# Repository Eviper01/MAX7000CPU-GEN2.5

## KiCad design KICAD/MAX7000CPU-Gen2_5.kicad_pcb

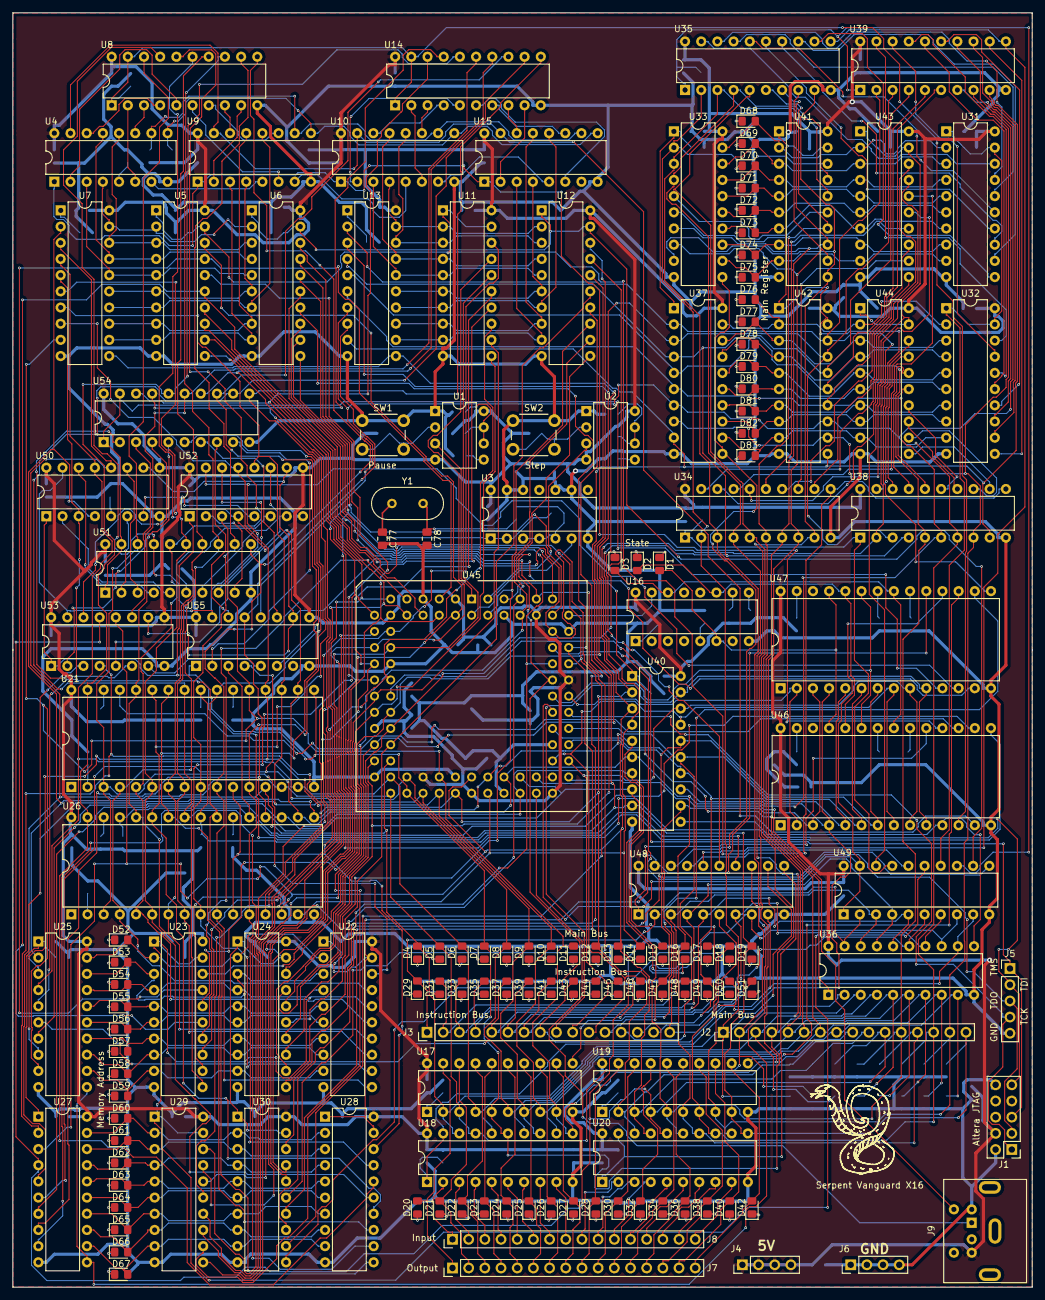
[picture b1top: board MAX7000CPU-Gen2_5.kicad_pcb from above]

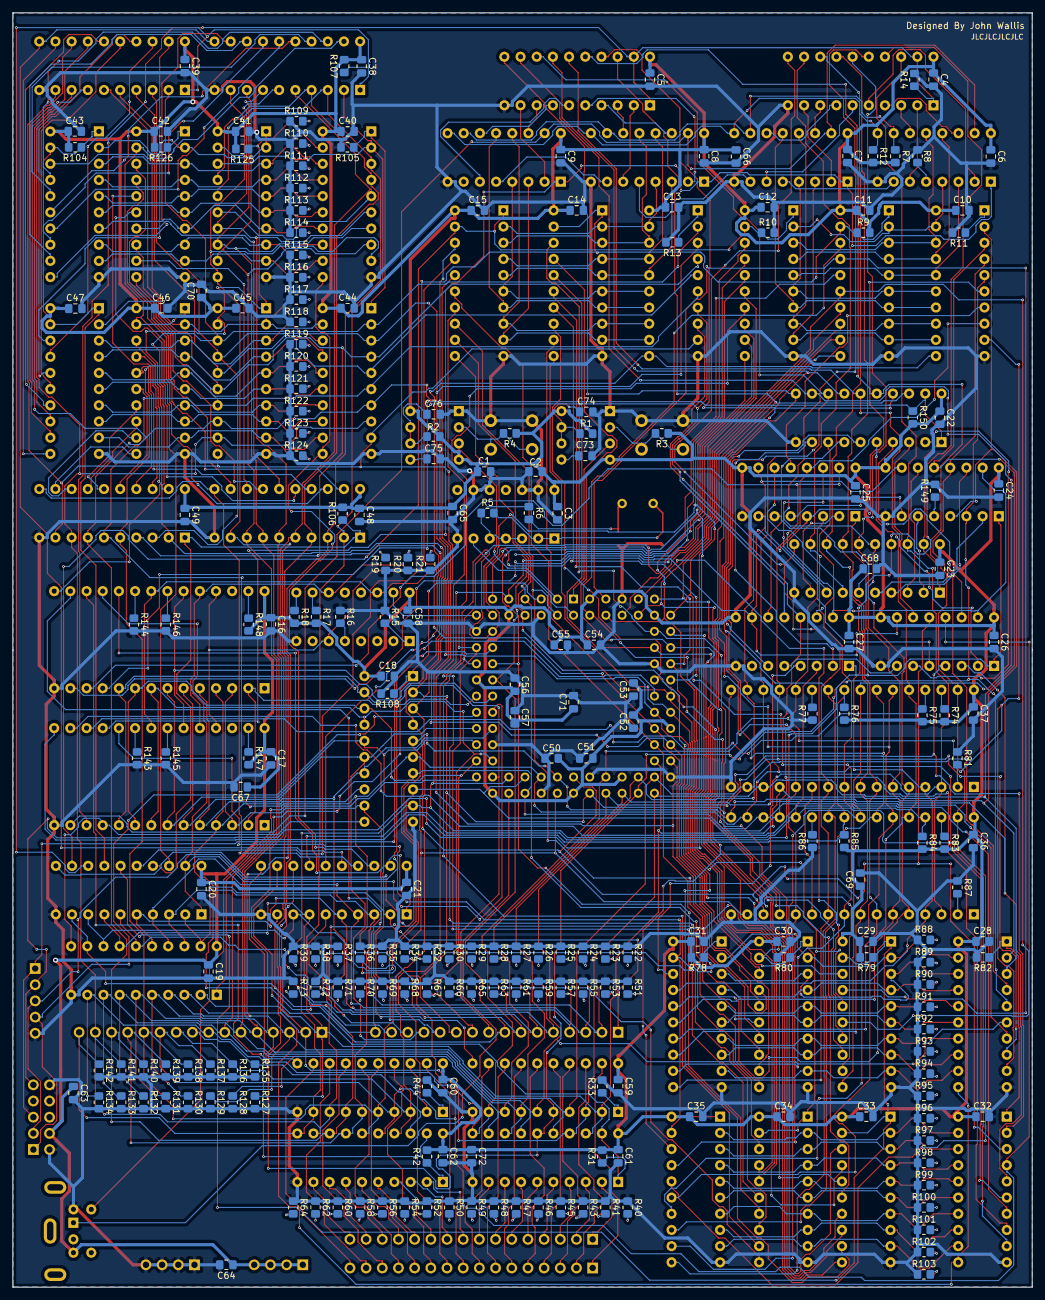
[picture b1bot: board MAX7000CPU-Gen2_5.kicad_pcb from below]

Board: 2 copper layers, 160.0 x 200.0 mm, 378 parts (226 on the bottom side), 398 nets.

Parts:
C1, C2, C3, C4, C5, C6, C7, C8, C9, C10, C11, C12, C13, C14, C15, C16, C17, C18, C19, C20, C21, C22, C23, C24, C25, C26, C27, C28, C29, C30, C31, C32, C33, C34, C35, C36, C37, C38, C39, C40, C41, C42, C43, C44, C45, C46, C47, C48, C49, C50, C51, C52, C53, C54, C55, C56, C57, C58, C59, C60, C61, C62, C63, C64, C74, C76: 100n; C_0805_2012Metric_Pad1.18x1.45mm_HandSolder
C65, C66, C67, C68, C69, C70, C71, C72: 10u; C_0805_2012Metric_Pad1.18x1.45mm_HandSolder
C73, C75: 10n; C_0805_2012Metric_Pad1.18x1.45mm_HandSolder
C77, C78: 33p; C_0805_2012Metric_Pad1.18x1.45mm_HandSolder
D1, D2, D3, D4, D5, D6, D7, D8, D9, D10, D11, D12, D13, D14, D15, D16, D17, D18, D19, D20, D21, D22, D23, D24, D25, D26, D27, D28, D29, D30, D31, D32, D33, D34, D35, D36, D37, D38, D39, D40, D41, D42, D43, D44, D45, D46, D47, D48, D49, D50, D51, D52, D53, D54, D55, D56, D57, D58, D59, D60, D61, D62, D63, D64, D65, D66, D67, D68, D69, D70, D71, D72, D73, D74, D75, D76, D77, D78, D79, D80, D81, D82, D83: LED; LED_0805_2012Metric_Pad1.15x1.40mm_HandSolder
J1: Conn_02x05_Odd_Even; PinHeader_2x05_P2.54mm_Vertical
J2, J3, J7, J8: Conn_01x16_Male; PinHeader_1x16_P2.54mm_Vertical
J4, J6: Conn_01x04_Male; PinHeader_1x04_P2.54mm_Vertical
J5: Conn_01x05_Male; PinHeader_1x05_P2.54mm_Vertical
J9: Mini-DIN-6; Connector_Mini-DIN_Female_6Pin_2rows
R1, R2, R5: 1M; R_0805_2012Metric_Pad1.20x1.40mm_HandSolder
R3, R4: 1K; R_0805_2012Metric_Pad1.20x1.40mm_HandSolder
R6: 4.7K; R_0805_2012Metric_Pad1.20x1.40mm_HandSolder
R7, R8, R9, R10, R11, R12, R13, R14, R15, R16, R17, R18, R31, R33, R42, R44, R74, R75, R76, R77, R78, R79, R80, R81, R82, R83, R84, R85, R86, R87, R104, R105, R106, R107, R108, R125, R126, R127, R128, R129, R130, R131, R132, R133, R134, R135, R136, R137, R138, R139, R140, R141, R142, R143, R144, R145, R146, R147, R148, R149, R150: 50K; R_0805_2012Metric_Pad1.20x1.40mm_HandSolder
R19, R20, R21, R22, R23, R24, R25, R26, R27, R28, R29, R30, R32, R34, R35, R36, R37, R38, R39, R40, R41, R43, R45, R46, R47, R48, R49, R50, R51, R52, R53, R54, R55, R56, R57, R58, R59, R60, R61, R62, R63, R64, R65, R66, R67, R68, R69, R70, R71, R72, R73, R88, R89, R90, R91, R92, R93, R94, R95, R96, R97, R98, R99, R100, R101, R102, R103, R109, R110, R111, R112, R113, R114, R115, R116, R117, R118, R119, R120, R121, R122, R123, R124: 330; R_0805_2012Metric_Pad1.20x1.40mm_HandSolder
SW1, SW2: SW_Push; SW_PUSH_6mm
U1, U2: NE555P; DIP-8_W7.62mm
U3: 74HC00; DIP-14_W7.62mm
U4, U9, U10, U15, U16, U50, U52, U53, U55: CD4029BEE4; DIP-16_W7.62mm
U5, U6, U8, U11, U12, U14, U18, U20, U22, U23, U24, U28, U29, U30, U31, U32, U41, U42, U43, U44, U48, U49, U51, U54: 74LS541; DIP-20_W7.62mm
U7, U13, U17, U19, U25, U27, U33, U34, U35, U36, U37, U38, U39, U40: 74LS574; DIP-20_W7.62mm
U21, U26: AS6C1008-55PCN; DIP-32_W15.24mm
U45: EPM7128slc84-15n; PLCC-84_THT-Socket
U46, U47: AT28C64B-15PU; DIP-28_W15.24mm
Y1: Crystal; Crystal_HC49-U_Vertical

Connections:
+5V: C1.1, C2.1, C3.1, C4.1, C5.1, C6.1, C7.1, C8.1, C9.1, C10.1, C11.1, C12.1, C13.1, C14.1, C15.1, C16.1, C17.1, C18.1, C19.1, C20.1, C21.1, C22.1, C23.1, C24.1, C25.1, C26.1, C27.1, C28.1, C29.1, C30.1, C31.1, C32.1, C33.1, C34.1, C35.1, C36.1, C37.1, C38.1, C39.1, C40.1, C41.1, C42.1, C43.1, C44.1, C45.1, C46.1, C47.1, C48.1, C49.1, C50.1, C51.1, C52.1, C53.1, C54.1, C55.1, C56.1, C57.1, C58.1, C59.1, C60.1, C61.1, C62.1, C63.1, C64.1, C65.1, C66.1, C67.1, C68.1, C69.1, C70.1, C71.1, C72.1, J1.4, J4.1, J4.2, J4.3, J4.4, J9.4, R1.1, R2.1, R3.1, R4.1, R7.2, R9.2, R12.2, R17.2, R18.2, R31.2, R42.2, R74.2, R75.2, R76.2, R78.2, R79.2, R83.2, R84.2, R85.2, R104.2, R106.2, R107.2, R125.2, R126.2, R147.2, R148.2, R150.2, U1.4, U1.8, U2.4, U2.8, U3.14, U4.16, U5.20, U6.20, U7.20, U8.20, U9.16, U10.16, U11.20, U12.20, U13.20, U14.20, U15.16, U16.16, U17.20, U18.20, U19.20, U20.20, U21.32, U22.20, U23.20, U24.20, U25.20, U26.32, U27.20, U28.20, U29.20, U30.20, U31.20, U32.20, U33.20, U34.20, U35.20, U36.20, U37.20, U38.20, U39.20, U40.20, U41.20, U42.20, U43.20, U44.20, U45.3, U45.13, U45.26, U45.38, U45.43, U45.53, U45.66, U45.78, U46.28, U47.28, U48.20, U49.20, U50.9, U50.16, U51.20, U52.9, U52.16, U53.9, U53.16, U54.20, U55.9, U55.16
/ALU/B0: D4.2, J2.1, R127.1, U7.2, U17.2, U18.18, U21.13, U25.2, U33.2, U34.2, U35.2, U36.2, U41.18, U45.31, U50.4
/ALU/B1: D5.2, J2.2, R128.1, U7.3, U17.3, U18.17, U21.14, U25.3, U33.3, U34.3, U35.3, U36.3, U41.17, U45.33, U50.12
/ALU/B2: D6.2, J2.3, R129.1, U7.4, U17.4, U18.16, U21.15, U25.4, U33.4, U34.4, U35.4, U36.4, U41.16, U45.34, U50.13
/ALU/B3: D7.2, J2.4, R130.1, U7.5, U17.5, U18.15, U21.17, U25.5, U33.5, U34.5, U35.5, U36.5, U41.15, U45.35, U50.3
/ALU/B4: D8.2, J2.5, R131.1, U7.6, U17.6, U18.14, U21.18, U25.6, U33.6, U34.6, U35.6, U36.6, U41.14, U45.36, U52.4
/ALU/B5: D9.2, J2.6, R132.1, U7.7, U17.7, U18.13, U21.19, U25.7, U33.7, U34.7, U35.7, U36.7, U41.13, U45.37, U52.12
/ALU/B6: D10.2, J2.7, R133.1, U7.8, U17.8, U18.12, U21.20, U25.8, U33.8, U34.8, U35.8, U36.8, U41.12, U45.39, U52.13
/ALU/B7: D11.2, J2.8, R134.1, U7.9, U17.9, U18.11, U21.21, U25.9, U33.9, U34.9, U35.9, U36.9, U41.11, U45.40, U52.3
/ALU/B8: D12.2, J2.9, R135.1, U13.2, U19.2, U20.18, U26.13, U27.2, U37.2, U38.2, U39.2, U40.2, U42.18, U45.41, U53.4
/ALU/B9: D13.2, J2.10, R136.1, U13.3, U19.3, U20.17, U26.14, U27.3, U37.3, U38.3, U39.3, U40.3, U42.17, U45.44, U53.12
/ALU/B10: D14.2, J2.11, R137.1, U13.4, U19.4, U20.16, U26.15, U27.4, U37.4, U38.4, U39.4, U40.4, U42.16, U45.45, U53.13
/ALU/B11: D15.2, J2.12, R138.1, U13.5, U19.5, U20.15, U26.17, U27.5, U37.5, U38.5, U39.5, U40.5, U42.15, U45.46, U53.3
/ALU/B12: D16.2, J2.13, R139.1, U13.6, U19.6, U20.14, U26.18, U27.6, U37.6, U38.6, U39.6, U40.6, U42.14, U45.48, U55.4
/ALU/B13: D17.2, J2.14, R140.1, U13.7, U19.7, U20.13, U26.19, U27.7, U37.7, U38.7, U39.7, U40.7, U42.13, U45.49, U55.12
/ALU/B14: D18.2, J2.15, R141.1, U13.8, U19.8, U20.12, U26.20, U27.8, U37.8, U38.8, U39.8, U40.8, U42.12, U45.50, U55.13
/ALU/B15: D19.2, J2.16, R142.1, U13.9, U19.9, U20.11, U26.21, U27.9, U37.9, U38.9, U39.9, U40.9, U42.11, U45.52, U55.3
/ALU/Ins0: D29.2, J3.1, U36.19, U48.2, U49.2
/ALU/Ins1: D31.2, J3.2, U36.18, U48.3, U49.3
/ALU/Ins2: D33.2, J3.3, U36.17, U48.4, U49.4
/ALU/Ins3: D35.2, J3.4, U36.16, U48.5, U49.5
/ALU/Ins4: D37.2, J3.5, U36.15, U48.6, U49.6
/ALU/Ins5: D39.2, J3.6, U36.14, U48.7, U49.7
/ALU/Ins6: D41.2, J3.7, U36.13, U48.8, U49.8
/ALU/Ins7: D43.2, J3.8, U36.12, U48.9, U49.9
/ALU/Ins8: D44.2, J3.9, U40.19, U45.55, U46.10, U47.10
/ALU/Ins9: D45.2, J3.10, U40.18, U45.56, U46.9, U47.9
/ALU/Ins10: D46.2, J3.11, U40.17, U45.57, U46.8, U47.8
/ALU/Ins11: D47.2, J3.12, U40.16, U45.58, U46.7, U47.7
/ALU/Ins12: D48.2, J3.13, U40.15, U45.60, U46.6, U47.6
/ALU/Ins13: D49.2, J3.14, U40.14, U45.61, U46.5, U47.5
/ALU/Ins14: D50.2, J3.15, U40.13, U46.4, U47.4
/ALU/Ins15: D51.2, J3.16, U40.12, U46.3, U47.3
/ALU/r_A0: U5.18, U23.18, U45.4
/ALU/r_A1: U5.17, U23.17, U45.5
/ALU/r_A2: U5.16, U23.16, U45.6
/ALU/r_A3: U5.15, U23.15, U45.8
/ALU/r_A4: U5.14, U23.14, U45.9
/ALU/r_A5: U5.13, U23.13, U45.10
/ALU/r_A6: U5.12, U23.12, U45.11
/ALU/r_A7: U5.11, U23.11, U45.12
/ALU/r_A8: U11.18, U29.18, U45.15
/ALU/r_A9: U11.17, U29.17, U45.16
/ALU/r_A10: U11.16, U29.16, U45.17
/ALU/r_A11: U11.15, U29.15, U45.18
/ALU/r_A12: U11.14, U29.14, U45.20
/ALU/r_A13: U11.13, U29.13, U45.21
/ALU/r_A14: U11.12, U29.12, U45.22
/ALU/r_A15: U11.11, U29.11, U45.24
/ALU/r_B0: U12.18, U24.18, U45.25
/ALU/r_B1: U12.17, U24.17, U45.27
/ALU/r_B2: U12.16, U24.16, U45.28
/ALU/r_B3: U12.15, U24.15, U45.29
/ALU/r_B4: U12.14, U24.14, U45.30
/ALU/r_B5: U12.13, U24.13, U45.84
/ALU/r_B6: U12.12, U24.12, U45.80
/ALU/r_B7: U12.11, U24.11, U45.79
/ALU/r_B8: U6.18, U30.18, U45.77
/ALU/r_B9: U6.17, U30.17, U45.76
/ALU/r_B10: U6.16, U30.16, U45.75
/ALU/r_B11: U6.15, U30.15, U45.73
/ALU/r_B12: U6.14, U30.14, U45.70
/ALU/r_B13: U6.13, U30.13, U45.69
/ALU/r_B14: U6.12, U30.12, U45.68
/ALU/r_B15: U6.11, U30.11, U45.67
/Counter Module/JB0: U4.4, U5.2, U6.2, U7.19
/Counter Module/JB1: U4.12, U5.3, U6.3, U7.18
/Counter Module/JB2: U4.13, U5.4, U6.4, U7.17
/Counter Module/JB3: U4.3, U5.5, U6.5, U7.16
/Counter Module/JB4: U5.6, U6.6, U7.15, U9.4
/Counter Module/JB5: U5.7, U6.7, U7.14, U9.12
/Counter Module/JB6: U5.8, U6.8, U7.13, U9.13
/Counter Module/JB7: U5.9, U6.9, U7.12, U9.3
/Counter Module/JB8: U10.4, U11.2, U12.2, U13.19
/Counter Module/JB9: U10.12, U11.3, U12.3, U13.18
/Counter Module/JB10: U10.13, U11.4, U12.4, U13.17
/Counter Module/JB11: U10.3, U11.5, U12.5, U13.16
/Counter Module/JB12: U11.6, U12.6, U13.15, U15.4
/Counter Module/JB13: U11.7, U12.7, U13.14, U15.12
/Counter Module/JB14: U11.8, U12.8, U13.13, U15.13
/Counter Module/JB15: U11.9, U12.9, U13.12, U15.3
/Counter Module/RA0: U8.18, U21.3, U22.18, U26.3, U51.18
/Counter Module/RA1: U8.17, U21.4, U22.17, U26.4, U51.17
/Counter Module/RA2: U8.16, U21.5, U22.16, U26.5, U51.16
/Counter Module/RA3: U8.15, U21.6, U22.15, U26.6, U51.15
/Counter Module/RA4: U8.14, U21.7, U22.14, U26.7, U51.14
/Counter Module/RA5: U8.13, U21.8, U22.13, U26.8, U51.13
/Counter Module/RA6: U8.12, U21.9, U22.12, U26.9, U51.12
/Counter Module/RA7: U8.11, U21.10, U22.11, U26.10, U51.11
/Counter Module/RA8: U14.18, U21.11, U26.11, U28.18, U54.18
/Counter Module/RA9: U14.17, U21.12, U26.12, U28.17, U54.17
/Counter Module/RA10: U14.16, U21.31, U26.31, U28.16, U54.16
/Counter Module/RA11: U14.15, U21.28, U26.28, U28.15, U54.15
/Counter Module/RA12: U14.14, U21.27, U26.27, U28.14, U54.14
/Counter Module/RA13: U14.13, U21.26, U26.26, U28.13, U54.13
/Counter Module/RA14: U14.12, U21.25, U26.25, U28.12, U54.12
/Counter Module/RA15: U14.11, U21.23, U26.23, U28.11, U54.11
/Counter Module/State0: D1.2, U16.6, U46.25, U47.25
/Counter Module/State1: D2.2, U16.11, U46.24, U47.24
/Counter Module/State2: D3.2, U16.14, U46.21, U47.21
/Interface/PI0: J8.1, U18.2
/Interface/PI1: J8.2, U18.3
/Interface/PI2: J8.3, U18.4
/Interface/PI3: J8.4, U18.5
/Interface/PI4: J8.5, U18.6
/Interface/PI5: J8.6, U18.7
/Interface/PI6: J8.7, U18.8
/Interface/PI7: J8.8, U18.9
/Interface/PI8: J8.9, U20.2
/Interface/PI9: J8.10, U20.3
/Interface/PI10: J8.11, U20.4
/Interface/PI11: J8.12, U20.5
/Interface/PI12: J8.13, U20.6
/Interface/PI13: J8.14, U20.7
/Interface/PI14: J8.15, U20.8
/Interface/PI15: J8.16, U20.9
/Interface/PO0: D20.2, J7.1, U17.19
/Interface/PO1: D21.2, J7.2, U17.18
/Interface/PO2: D22.2, J7.3, U17.17
/Interface/PO3: D23.2, J7.4, U17.16
/Interface/PO4: D24.2, J7.5, U17.15
/Interface/PO5: D25.2, J7.6, U17.14
/Interface/PO6: D26.2, J7.7, U17.13
/Interface/PO7: D27.2, J7.8, U17.12
/Interface/PO8: D28.2, J7.9, U19.19
/Interface/PO9: D30.2, J7.10, U19.18
/Interface/PO10: D32.2, J7.11, U19.17
/Interface/PO11: D34.2, J7.12, U19.16
/Interface/PO12: D36.2, J7.13, U19.15
/Interface/PO13: D38.2, J7.14, U19.14
/Interface/PO14: D40.2, J7.15, U19.13
/Interface/PO15: D42.2, J7.16, U19.12
/Memory/MA0: D52.2, U22.2, U23.2, U24.2, U25.19
/Memory/MA1: D53.2, U22.3, U23.3, U24.3, U25.18
/Memory/MA2: D54.2, U22.4, U23.4, U24.4, U25.17
/Memory/MA3: D55.2, U22.5, U23.5, U24.5, U25.16
/Memory/MA4: D56.2, U22.6, U23.6, U24.6, U25.15
/Memory/MA5: D57.2, U22.7, U23.7, U24.7, U25.14
/Memory/MA6: D58.2, U22.8, U23.8, U24.8, U25.13
/Memory/MA7: D59.2, U22.9, U23.9, U24.9, U25.12
/Memory/MA8: D60.2, U27.19, U28.2, U29.2, U30.2
/Memory/MA9: D61.2, U27.18, U28.3, U29.3, U30.3
/Memory/MA10: D62.2, U27.17, U28.4, U29.4, U30.4
/Memory/MA11: D63.2, U27.16, U28.5, U29.5, U30.5
/Memory/MA12: D64.2, U27.15, U28.6, U29.6, U30.6
/Memory/MA13: D65.2, U27.14, U28.7, U29.7, U30.7
/Memory/MA14: D66.2, U27.13, U28.8, U29.8, U30.8
/Memory/MA15: D67.2, U27.12, U28.9, U29.9, U30.9
/Registers/MR0: D68.2, U31.2, U33.19, U41.2, U43.2
/Registers/MR1: D69.2, U31.3, U33.18, U41.3, U43.3
/Registers/MR2: D70.2, U31.4, U33.17, U41.4, U43.4
/Registers/MR3: D71.2, U31.5, U33.16, U41.5, U43.5
/Registers/MR4: D72.2, U31.6, U33.15, U41.6, U43.6
/Registers/MR5: D73.2, U31.7, U33.14, U41.7, U43.7
/Registers/MR6: D74.2, U31.8, U33.13, U41.8, U43.8
/Registers/MR7: D75.2, U31.9, U33.12, U41.9, U43.9
/Registers/MR8: D76.2, U32.2, U37.19, U42.2, U44.2
/Registers/MR9: D77.2, U32.3, U37.18, U42.3, U44.3
/Registers/MR10: D78.2, U32.4, U37.17, U42.4, U44.4
/Registers/MR11: D79.2, U32.5, U37.16, U42.5, U44.5
/Registers/MR12: D80.2, U32.6, U37.15, U42.6, U44.6
/Registers/MR13: D81.2, U32.7, U37.14, U42.7, U44.7
/Registers/MR14: D82.2, U32.8, U37.13, U42.8, U44.8
/Registers/MR15: D83.2, U32.9, U37.12, U42.9, U44.9
/Registers/rA0: U34.19, U43.18
/Registers/rA1: U34.18, U43.17
/Registers/rA2: U34.17, U43.16
/Registers/rA3: U34.16, U43.15
/Registers/rA4: U34.15, U43.14
/Registers/rA5: U34.14, U43.13
/Registers/rA6: U34.13, U43.12
/Registers/rA7: U34.12, U43.11
/Registers/rA8: U38.19, U44.18
/Registers/rA9: U38.18, U44.17
/Registers/rA10: U38.17, U44.16
/Registers/rA11: U38.16, U44.15
/Registers/rA12: U38.15, U44.14
/Registers/rA13: U38.14, U44.13
/Registers/rA14: U38.13, U44.12
/Registers/rA15: U38.12, U44.11
/Registers/rB0: U31.18, U35.19
/Registers/rB1: U31.17, U35.18
/Registers/rB2: U31.16, U35.17
/Registers/rB3: U31.15, U35.16
/Registers/rB4: U31.14, U35.15
/Registers/rB5: U31.13, U35.14
/Registers/rB6: U31.12, U35.13
/Registers/rB7: U31.11, U35.12
/Registers/rB8: U32.18, U39.19
/Registers/rB9: U32.17, U39.18
/Registers/rB10: U32.16, U39.17
/Registers/rB11: U32.15, U39.16
/Registers/rB12: U32.14, U39.15
/Registers/rB13: U32.13, U39.14
/Registers/rB14: U32.12, U39.13
/Registers/rB15: U32.11, U39.12
ALU_Regs: U45.63, U47.18, U49.1, U49.19
CLK: U16.15, U45.74
CLK_Select: U1.3, U45.1
Count: U4.15, U9.15, U10.15, U15.15, U46.13
CounterOutControl: R14.1, U8.1, U8.19, U14.1, U14.19, U46.12
EqualFlag: U45.65, U46.23, U47.23
FastCLK: U3.6, U45.2
GND: C1.2, C2.2, C3.2, C4.2, C5.2, C6.2, C7.2, C8.2, C9.2, C10.2, C11.2, C12.2, C13.2, C14.2, C15.2, C16.2, C17.2, C18.2, C19.2, C20.2, C21.2, C22.2, C23.2, C24.2, C25.2, C26.2, C27.2, C28.2, C29.2, C30.2, C31.2, C32.2, C33.2, C34.2, C35.2, C36.2, C37.2, C38.2, C39.2, C40.2, C41.2, C42.2, C43.2, C44.2, C45.2, C46.2, C47.2, C48.2, C49.2, C50.2, C51.2, C52.2, C53.2, C54.2, C55.2, C56.2, C57.2, C58.2, C59.2, C60.2, C61.2, C62.2, C63.2, C64.2, C65.2, C66.2, C67.2, C68.2, C69.2, C70.2, C71.2, C72.2, C73.2, C74.2, C75.2, C76.2, C77.2, C78.2, J1.2, J1.10, J5.5, J6.1, J6.2, J6.3, J6.4, J9.3, R8.2, R10.2, R11.2, R13.2, R14.2, R15.2, R16.2, R19.1, R20.1, R21.1, R22.1, R23.1, R24.1, R25.1, R26.1, R27.1, R28.1, R29.1, R30.1, R32.1, R33.2, R34.1, R35.1, R36.1, R37.1, R38.1, R39.1, R40.1, R41.1, R43.1, R44.2, R45.1, R46.1, R47.1, R48.1, R49.1, R50.1, R51.1, R52.1, R53.1, R54.1, R55.1, R56.1, R57.1, R58.1, R59.1, R60.1, R61.1, R62.1, R63.1, R64.1, R65.1, R66.1, R67.1, R68.1, R69.1, R70.1, R71.1, R72.1, R73.1, R77.1, R80.2, R81.1, R82.2, R86.1, R87.1, R88.1, R89.1, R90.1, R91.1, R92.1, R93.1, R94.1, R95.1, R96.1, R97.1, R98.1, R99.1, R100.1, R101.1, R102.1, R103.1, R105.2, R108.2, R109.1, R110.1, R111.1, R112.1, R113.1, R114.1, R115.1, R116.1, R117.1, R118.1, R119.1, R120.1, R121.1, R122.1, R123.1, R124.1, R127.2, R128.2, R129.2, R130.2, R131.2, R132.2, R133.2, R134.2, R135.2, R136.2, R137.2, R138.2, R139.2, R140.2, R141.2, R142.2, R143.2, R144.2, R145.2, R146.2, R149.2, SW1.1, SW2.1, U1.1, U2.1, U3.7, U3.9, U3.10, U3.12, U3.13, U4.8, U5.10, U6.10, U7.10, U8.10, U9.8, U10.8, U11.10, U12.10, U13.10, U14.10, U15.8, U16.8, U17.10, U18.10, U19.10, U20.10, U21.16, U22.10, U23.10, U24.10, U25.10, U26.16, U27.10, U28.10, U29.10, U30.10, U31.10, U32.10, U33.10, U34.10, U35.10, U36.10, U37.10, U38.10, U39.10, U40.10, U41.10, U42.10, U43.10, U44.10, U45.7, U45.19, U45.32, U45.42, U45.47, U45.59, U45.72, U45.82, U46.14, U47.14, U48.10, U49.10, U50.8, U51.10, U52.8, U53.8, U54.10, U55.8
I2CCLK: J9.5, U45.54
I2CData: J9.1, U45.51
InsRegControl: U36.11, U40.11, U46.11
JumpBufferAOutput: R9.1, U5.1, U5.19, U11.1, U11.19, U49.16
JumpBufferBOutput: R10.1, U6.1, U6.19, U12.1, U12.19, U49.12
JumpEnable: U4.1, U9.1, U10.1, U15.1, U46.18
JumpRegLoad: U7.11, U13.11, U48.15
MainAOutput: R126.1, U43.1, U43.19, U44.1, U44.19, U49.18
MainBOutput: R104.1, U31.1, U31.19, U32.1, U32.19, U49.14
MainRegOutputControl: R125.1, U41.1, U41.19, U42.1, U42.19, U47.15
MainRegReadControl: U33.11, U37.11, U48.18
MemAddrAOutput: R79.1, U23.1, U23.19, U29.1, U29.19, U49.15
MemAddrBOutput: R80.1, U24.1, U24.19, U30.1, U30.19, U49.11
MemOutEnable: R76.1, R85.1, U21.24, U26.24, U46.15
MemWriteControlH: R84.1, U26.29, U46.16
MemWriteControlL: R75.1, U21.29, U46.17
unnamed: C73.1, U1.5
unnamed: C74.1, R1.2, U1.6, U1.7
unnamed: C75.1, U2.5
unnamed: C76.1, R2.2, U2.6, U2.7
unnamed: C77.1, R5.2, U3.1, U3.2, Y1.1
unnamed: C78.1, R6.2, Y1.2
unnamed: D1.1, R19.2
unnamed: D2.1, R20.2
unnamed: D3.1, R21.2
unnamed: D4.1, R22.2
unnamed: D5.1, R23.2
unnamed: D6.1, R24.2
unnamed: D7.1, R25.2
unnamed: D8.1, R26.2
unnamed: D9.1, R27.2
unnamed: D10.1, R28.2
unnamed: D11.1, R29.2
unnamed: D12.1, R30.2
unnamed: D13.1, R32.2
unnamed: D14.1, R34.2
unnamed: D15.1, R35.2
unnamed: D16.1, R36.2
unnamed: D17.1, R37.2
unnamed: D18.1, R38.2
unnamed: D19.1, R39.2
unnamed: D20.1, R40.2
unnamed: D21.1, R41.2
unnamed: D22.1, R43.2
unnamed: D23.1, R45.2
unnamed: D24.1, R46.2
unnamed: D25.1, R47.2
unnamed: D26.1, R48.2
unnamed: D27.1, R49.2
unnamed: D28.1, R50.2
unnamed: D29.1, R51.2
unnamed: D30.1, R52.2
unnamed: D31.1, R53.2
unnamed: D32.1, R54.2
unnamed: D33.1, R55.2
unnamed: D34.1, R56.2
unnamed: D35.1, R57.2
unnamed: D36.1, R58.2
unnamed: D37.1, R59.2
unnamed: D38.1, R60.2
unnamed: D39.1, R61.2
unnamed: D40.1, R62.2
unnamed: D41.1, R63.2
unnamed: D42.1, R64.2
unnamed: D43.1, R65.2
unnamed: D44.1, R66.2
unnamed: D45.1, R67.2
unnamed: D46.1, R68.2
unnamed: D47.1, R69.2
unnamed: D48.1, R70.2
unnamed: D49.1, R71.2
unnamed: D50.1, R72.2
unnamed: D51.1, R73.2
unnamed: D52.1, R88.2
unnamed: D53.1, R89.2
unnamed: D54.1, R90.2
unnamed: D55.1, R91.2
unnamed: D56.1, R92.2
unnamed: D57.1, R93.2
unnamed: D58.1, R94.2
unnamed: D59.1, R95.2
unnamed: D60.1, R96.2
unnamed: D61.1, R97.2
unnamed: D62.1, R98.2
unnamed: D63.1, R99.2
unnamed: D64.1, R100.2
unnamed: D65.1, R101.2
unnamed: D66.1, R102.2
unnamed: D67.1, R103.2
unnamed: D68.1, R109.2
unnamed: D69.1, R110.2
unnamed: D70.1, R111.2
unnamed: D71.1, R112.2
unnamed: D72.1, R113.2
unnamed: D73.1, R114.2
unnamed: D74.1, R115.2
unnamed: D75.1, R116.2
unnamed: D76.1, R117.2
unnamed: D77.1, R118.2
unnamed: D78.1, R119.2
unnamed: D79.1, R120.2
unnamed: D80.1, R121.2
unnamed: D81.1, R122.2
unnamed: D82.1, R123.2
unnamed: D83.1, R124.2
unnamed: R3.2, SW1.2, U1.2
unnamed: R4.2, SW2.2, U2.2
unnamed: R5.1, R6.1, U3.3, U3.4, U3.5
unnamed: R7.1, U4.10, U9.10, U10.10, U15.10
unnamed: R8.1, U4.5
unnamed: R11.1, U7.1
unnamed: R12.1, U4.9, U9.9, U10.9, U15.9
unnamed: R13.1, U13.1
unnamed: R15.1, U16.1
unnamed: R16.1, U16.5
unnamed: R17.1, U16.10
unnamed: R18.1, U16.9
unnamed: R33.1, U17.1
unnamed: R44.1, U19.1
unnamed: R74.1, U21.30
unnamed: R77.2, U21.22
unnamed: R81.2, U21.2
unnamed: R82.1, U25.1, U27.1
unnamed: R83.1, U26.30
unnamed: R86.2, U26.22
unnamed: R87.2, U26.2
unnamed: R105.1, U33.1, U37.1
unnamed: R143.1, U46.20
unnamed: R144.1, U47.20
unnamed: R145.1, U46.22
unnamed: R146.1, U47.22
unnamed: R147.1, U46.27
unnamed: R148.1, U47.27
unnamed: R149.1, U50.5
unnamed: U4.2, U8.5
unnamed: U4.6, U8.2
unnamed: U4.7, U9.5
unnamed: U4.11, U8.3
unnamed: U4.14, U8.4
unnamed: U8.6, U9.6
unnamed: U8.7, U9.11
unnamed: U8.8, U9.14
unnamed: U8.9, U9.2
unnamed: U10.2, U14.5
unnamed: U9.7, U10.5
unnamed: U10.6, U14.2
unnamed: U10.7, U15.5
unnamed: U10.11, U14.3
unnamed: U10.14, U14.4
unnamed: U14.6, U15.6
unnamed: U14.7, U15.11
unnamed: U14.8, U15.14
unnamed: U14.9, U15.2
unnamed: U50.2, U51.5
unnamed: U50.6, U51.2
unnamed: U50.7, U52.5
unnamed: U50.11, U51.3
unnamed: U50.14, U51.4
unnamed: U51.6, U52.6
unnamed: U51.7, U52.11
unnamed: U51.8, U52.14
unnamed: U51.9, U52.2
unnamed: U52.7, U53.5
unnamed: U53.2, U54.5
unnamed: U53.6, U54.2
unnamed: U53.7, U55.5
unnamed: U53.11, U54.3
unnamed: U53.14, U54.4
unnamed: U54.6, U55.6
unnamed: U54.7, U55.11
unnamed: U54.8, U55.14
unnamed: U54.9, U55.2
OverflowFlag: U45.64, U46.2, U47.2
PortALatch: U17.11, U47.16
PortBLatch: U19.11, U47.17
PortCRead: R31.1, U18.1, U18.19, U48.12
PortDRead: R42.1, U20.1, U20.19, U48.11
ProgramEnable: R108.1, U36.1, U40.1, U45.81
R1Output: R106.1, U34.1, U38.1, U49.17
R1ReadControl: U34.11, U38.11, U48.17
R2Output: R107.1, U35.1, U39.1, U49.13
R2ReadControl: U35.11, U39.11, U48.16
RAM_Addr_Enable: R78.1, U22.1, U22.19, U28.1, U28.19, U46.19
Ram_Addr_Read: U25.11, U27.11, U48.13
RegRead: U47.19, U48.1, U48.19
StackCount: U47.12, U50.15, U52.15, U53.15, U55.15
StackCountDirection: U47.13, U50.10, U52.10, U53.10, U55.10
StackJump: U48.14, U50.1, U52.1, U53.1, U55.1
StackOutControl: R150.1, U47.11, U51.1, U51.19, U54.1, U54.19
TCK: J1.1, J5.4, U45.62
TDI: J1.9, J5.2, U45.14
TDO: J1.3, J5.3, U45.71
TMS: J1.5, J5.1, U45.23
UserCLK: U2.3, U45.83

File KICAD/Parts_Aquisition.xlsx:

Source: | E:\Libraries\Documents\MAX7000CPU-GEN2.5\KICAD\MAX7000CPU-Gen2_5.sch
Date: | 44622.676400462966
Tool: | Eeschema (5.1.10)-1
Generator: | C:\Program Files\KiCad\bin\scripting\plugins/bom_csv_grouped_by_value.py
Component Count: | 378
Collated Components:
Item | Qty | Reference(s) | Value | Unit Price (USD) | Total (USD) | Inventory | Location
1 | 66 | C1, C2, C3, C4, C5, C6, C7, C8, C9, C10, C11, C12, C13, C14, C15, C16, C17, C18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 | 100n | 8.4700000000000001E-3 | 0.55901999999999996 | 0 | https://www.aliexpress.com/item/32964553793.html?spm=a2g0o.9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
2 | 8 | C65, C66, C67, C68, C69, C70, C71, C72 | 10u | 1.3860000000000001E-2 | 0.11088000000000001 | 0 | https://www.aliexpress.com/item/32964553793.html?spm=a2g0o.9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
3 | 2 | C73, C75 | 10n | 8.4700000000000001E-3 | 1.694E-2 | 0 | https://www.aliexpress.com/item/32964553793.html?spm=a2g0o.9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
4 | 2 | C77, C78 | 33p | 8.4700000000000001E-3 | 1.694E-2 | 1 | https://www.aliexpress.com/item/32964553793.html?spm=a2g0o.9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
5 | 83 | D1, D2, D3, D4, D5, D6, D7, D8, D9, D10, D11, D12, D13, D14, D15, D16, D17, D18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 | LED | 7.8722891566265062E-3 | 0.65339999999999998 | 1 | https://www.aliexpress.com/item/4000927747306.html?spm=a2g0o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
6 | 1 | J1 | Conn_02x05_Odd_Even | 0 | 0 | 1 | https://www.aliexpress.com/item/32670970932.html?spm=a2g0o.9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
7 | 4 | J2, J3, J7, J8 | Conn_01x16_Male | 0 | 0 | 1 | https://www.aliexpress.com/item/32670970932.html?spm=a2g0o.9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
8 | 2 | J4, J6 | Conn_01x04_Male | 0 | 0 | 1 | https://www.aliexpress.com/item/32670970932.html?spm=a2g0o.9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
9 | 1 | J5 | Conn_01x05_Male | 0 | 0 | 1 | https://www.aliexpress.com/item/32670970932.html?spm=a2g0o.9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
10 | 1 | J9 | Mini-DIN-6 | 3.1019999999999999 | 3.1019999999999999 | 0 | https://www.aliexpress.com/item/1005001769865560.html?spm=a2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 |  |  |  |  |  |  |  |  |  |  | MDC-6-02
11 | 3 | R1, R2, R5 | 1M | 4.5100000000000001E-3 | 1.353E-2 | 0 | https://www.aliexpress.com/item/32865947306.html?spm=a2g0o.9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
12 | 2 | R3, R4 | 1K | 4.5100000000000001E-3 | 9.0200000000000002E-3 | 1 | https://www.aliexpress.com/item/32865947306.html?spm=a2g0o.9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
13 | 1 | R6 | 4.7K | 4.5100000000000001E-3 | 4.5100000000000001E-3 | 0 | https://www.aliexpress.com/item/32865947306.html?spm=a2g0o.9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
14 | 61 | R7, R8, R9, R10, R11, R12, R13, R14, R15, R16, R17, R18, R31, R33, R42, R44, R7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 | 50K | 4.5100000000000001E-3 | 0.27511000000000002 | 0 | https://www.aliexpress.com/item/32865947306.html?spm=a2g0o.9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
15 | 83 | R19, R20, R21, R22, R23, R24, R25, R26, R27, R28, R29, R30, R32, R34, R35, R36,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 | 330 . | 4.5100000000000001E-3 | 0.37433 | 1 | https://www.aliexpress.com/item/32865947306.html?spm=a2g0o.9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
16 | 2 | SW1, SW2 | SW_Push | 7.5350000000000014E-2 | 0.15070000000000003 | 1 | https://www.aliexpress.com/item/32657892064.html?spm=a2g0o.9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
17 | 2 | U1, U2 | NE555P | 0.14190000000000003 | 0.28380000000000005 | 1 | https://www.aliexpress.com/item/1005002606088465.html?spm=a2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
18 | 1 | U3 | 74HC00 | 0.2387 | 0.2387 | 1 | https://www.aliexpress.com/item/1005001436948748.html?spm=a2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
19 | 9 | U4, U9, U10, U15, U16, U50, U52, U53, U55 | CD4029BEE4 | 0.3861 | 3.4748999999999999 | 0 | https://www.aliexpress.com/item/32545018073.html?spm=a2g0o.c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
20 | 24 | U5, U6, U8, U11, U12, U14, U18, U20, U22, U23, U24, U28, U29, U30, U31, U32, U4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 | 74LS541 | 0.35221999999999998 | 8.4532799999999995 | 0 | https://www.aliexpress.com/item/1005002119723623.html?spm=a2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
21 | 14 | U7, U13, U17, U19, U25, U27, U33, U34, U35, U36, U37, U38, U39, U40 | 74LS574 | 0.36409999999999998 | 5.0973999999999995 | 0 | https://www.aliexpress.com/item/1005002119796388.html?spm=a2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
22 | 2 | U21, U26 | AS6C1008-55PCN | 2.6905999999999999 | 5.3811999999999998 | 1 | https://www.aliexpress.com/item/4001000401517.html?spm=a2g0o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
23 | 1 | U45 | EPM7128slc84-15n | 1.8699999999999999 | 1.8699999999999999 | 1 | https://www.ebay.com.au/itm/401600686549
24 | 2 | U46, U47 | AT28C64B-15PU | 1.5246 | 3.0491999999999999 | 1 | https://www.aliexpress.com/item/1005002059804323.html?spm=a2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
25 | 1 | Y1 | Crystal | 0.60719999999999996 | 0.60719999999999996 | 1 | https://www.aliexpress.com/item/32620439167.html?spm=a2g0o.p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
26* | 2 |  | Dip 32 Socket | 0.24310000000000001 | 0.48620000000000002 | 1 | https://www.aliexpress.com/item/1005001726382472.html?spm=a2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
27* | 2 |  | Dip 28 Socket |  | 0 | 0 | https://www.aliexpress.com/item/32917069084.html?spm=a2g0o.c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
28* | 1 |  | PLCC-84 Socket | 0.95919999999999983 | 0.95919999999999983 | 1 | https://www.aliexpress.com/item/4000272069732.html?spm=a2g0o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
 | Total | 35.187460000000002
 | Total (Backorder) | 21.107570000000003

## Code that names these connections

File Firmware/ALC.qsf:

# -------------------------------------------------------------------------- #
#
# Copyright (C) 1991-2013 Altera Corporation
# Your use of Altera Corporation's design tools, logic functions 
# and other software and tools, and its AMPP partner logic 
# functions, and any output files from any of the foregoing 
# (including device programming or simulation files), and any 
# associated documentation or information are expressly subject 
# to the terms and conditions of the Altera Program License 
# Subscription Agreement, Altera MegaCore Function License 
# Agreement, or other applicable license agreement, including, 
# without limitation, that your use is for the sole purpose of 
# programming logic devices manufactured by Altera and sold by 
# Altera or its authorized distributors.  Please refer to the 
# applicable agreement for further details.
#
# -------------------------------------------------------------------------- #
#
# Quartus II 64-Bit
# Version 13.0.1 Build 232 06/12/2013 Service Pack 1 SJ Web Edition
# Date created = 18:09:41  April 16, 2022
#
# -------------------------------------------------------------------------- #
#
# Notes:
#
# 1) The default values for assignments are stored in the file:
#		ALC_assignment_defaults.qdf
#    If this file doesn't exist, see file:
#		assignment_defaults.qdf
#
# 2) Altera recommends that you do not modify this file. This
#    file is updated automatically by the Quartus II software
#    and any changes you make may be lost or overwritten.
#
# -------------------------------------------------------------------------- #


set_global_assignment -name FAMILY MAX7000S
set_global_assignment -name DEVICE "EPM7128SLC84-15"
set_global_assignment -name TOP_LEVEL_ENTITY ALC
set_global_assignment -name ORIGINAL_QUARTUS_VERSION "13.0 SP1"
set_global_assignment -name PROJECT_CREATION_TIME_DATE "18:09:41  APRIL 16, 2022"
set_global_assignment -name LAST_QUARTUS_VERSION "13.0 SP1"
set_global_assignment -name PROJECT_OUTPUT_DIRECTORY output_files
set_global_assignment -name DEVICE_FILTER_PACKAGE PLCC
set_global_assignment -name DEVICE_FILTER_PIN_COUNT 84
set_global_assignment -name DEVICE_FILTER_SPEED_GRADE 15
set_global_assignment -name ERROR_CHECK_FREQUENCY_DIVISOR "-1"
set_global_assignment -name EDA_DESIGN_ENTRY_SYNTHESIS_TOOL "Design Compiler"
set_global_assignment -name EDA_INPUT_VCC_NAME VDD -section_id eda_design_synthesis
set_global_assignment -name EDA_LMF_FILE altsyn.lmf -section_id eda_design_synthesis
set_global_assignment -name EDA_INPUT_DATA_FORMAT VHDL -section_id eda_design_synthesis
set_global_assignment -name EDA_SIMULATION_TOOL "ModelSim-Altera (VHDL)"
set_global_assignment -name EDA_OUTPUT_DATA_FORMAT VHDL -section_id eda_simulation
set_global_assignment -name OPTIMIZE_HOLD_TIMING OFF
set_global_assignment -name OPTIMIZE_MULTI_CORNER_TIMING OFF
set_global_assignment -name FITTER_EFFORT "STANDARD FIT"
set_global_assignment -name MAX7000_DEVICE_IO_STANDARD TTL
set_location_assignment PIN_63 -to ALU_Regs
set_location_assignment PIN_74 -to CLK
set_location_assignment PIN_1 -to CLK_Select
set_location_assignment PIN_65 -to EqualFlag
set_location_assignment PIN_2 -to FastCLK
set_location_assignment PIN_54 -to I2CCLK
set_location_assignment PIN_51 -to I2CData
set_location_assignment PIN_61 -to Ins[5]
set_location_assignment PIN_60 -to Ins[4]
set_location_assignment PIN_58 -to Ins[3]
set_location_assignment PIN_57 -to Ins[2]
set_location_assignment PIN_56 -to Ins[1]
set_location_assignment PIN_55 -to Ins[0]
set_location_assignment PIN_52 -to MainBus[15]
set_location_assignment PIN_50 -to MainBus[14]
set_location_assignment PIN_49 -to MainBus[13]
set_location_assignment PIN_48 -to MainBus[12]
set_location_assignment PIN_46 -to MainBus[11]
set_location_assignment PIN_45 -to MainBus[10]
set_location_assignment PIN_44 -to MainBus[9]
set_location_assignment PIN_41 -to MainBus[8]
set_location_assignment PIN_40 -to MainBus[7]
set_location_assignment PIN_39 -to MainBus[6]
set_location_assignment PIN_37 -to MainBus[5]
set_location_assignment PIN_36 -to MainBus[4]
set_location_assignment PIN_35 -to MainBus[3]
set_location_assignment PIN_34 -to MainBus[2]
set_location_assignment PIN_33 -to MainBus[1]
set_location_assignment PIN_31 -to MainBus[0]
set_location_assignment PIN_64 -to OverflowFlag
set_location_assignment PIN_24 -to regA[15]
set_location_assignment PIN_22 -to regA[14]
set_location_assignment PIN_21 -to regA[13]
set_location_assignment PIN_20 -to regA[12]
set_location_assignment PIN_18 -to regA[11]
set_location_assignment PIN_17 -to regA[10]
set_location_assignment PIN_16 -to regA[9]
set_location_assignment PIN_15 -to regA[8]
set_location_assignment PIN_12 -to regA[7]
set_location_assignment PIN_11 -to regA[6]
set_location_assignment PIN_10 -to regA[5]
set_location_assignment PIN_9 -to regA[4]
set_location_assignment PIN_8 -to regA[3]
set_location_assignment PIN_6 -to regA[2]
set_location_assignment PIN_5 -to regA[1]
set_location_assignment PIN_4 -to regA[0]
set_location_assignment PIN_67 -to regB[15]
set_location_assignment PIN_68 -to regB[14]
set_location_assignment PIN_69 -to regB[13]
set_location_assignment PIN_70 -to regB[12]
set_location_assignment PIN_73 -to regB[11]
set_location_assignment PIN_75 -to regB[10]
set_location_assignment PIN_76 -to regB[9]
set_location_assignment PIN_77 -to regB[8]
set_location_assignment PIN_79 -to regB[7]
set_location_assignment PIN_80 -to regB[6]
set_location_assignment PIN_84 -to regB[5]
set_location_assignment PIN_30 -to regB[4]
set_location_assignment PIN_29 -to regB[3]
set_location_assignment PIN_28 -to regB[2]
set_location_assignment PIN_27 -to regB[1]
set_location_assignment PIN_25 -to regB[0]
set_location_assignment PIN_62 -to TCK
set_location_assignment PIN_14 -to TDI
set_location_assignment PIN_71 -to TDO
set_location_assignment PIN_23 -to TMS
set_location_assignment PIN_83 -to UserCLK
set_global_assignment -name VHDL_FILE "HDL-Files/uALU.vhdl"
set_global_assignment -name VERILOG_FILE "HDL-Files/ALU.verilog"
set_global_assignment -name VHDL_FILE "HDL-Files/logic.vhdl"
set_global_assignment -name VHDL_FILE "HDL-Files/ALC.vhdl"
set_global_assignment -name CDF_FILE output_files/Chain1.cdf
set_global_assignment -name VHDL_INPUT_VERSION VHDL_1993
set_global_assignment -name VHDL_SHOW_LMF_MAPPING_MESSAGES OFF

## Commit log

2022-04-16 Commit Setup (No Libraries)
2022-04-16 Commit Setup (Adding Libraries)
2022-04-17 ALC draft
2022-04-18 BOM update
2022-04-21 First Version of Compiler
2022-04-30 Microcode and hardware issues
2022-06-27 A few changes to notes
2022-06-28 Microcode Hexfile Generator
2022-06-28 gitignore
2022-06-28 gitactuallignore
2022-06-30 ALC heavy modifications
